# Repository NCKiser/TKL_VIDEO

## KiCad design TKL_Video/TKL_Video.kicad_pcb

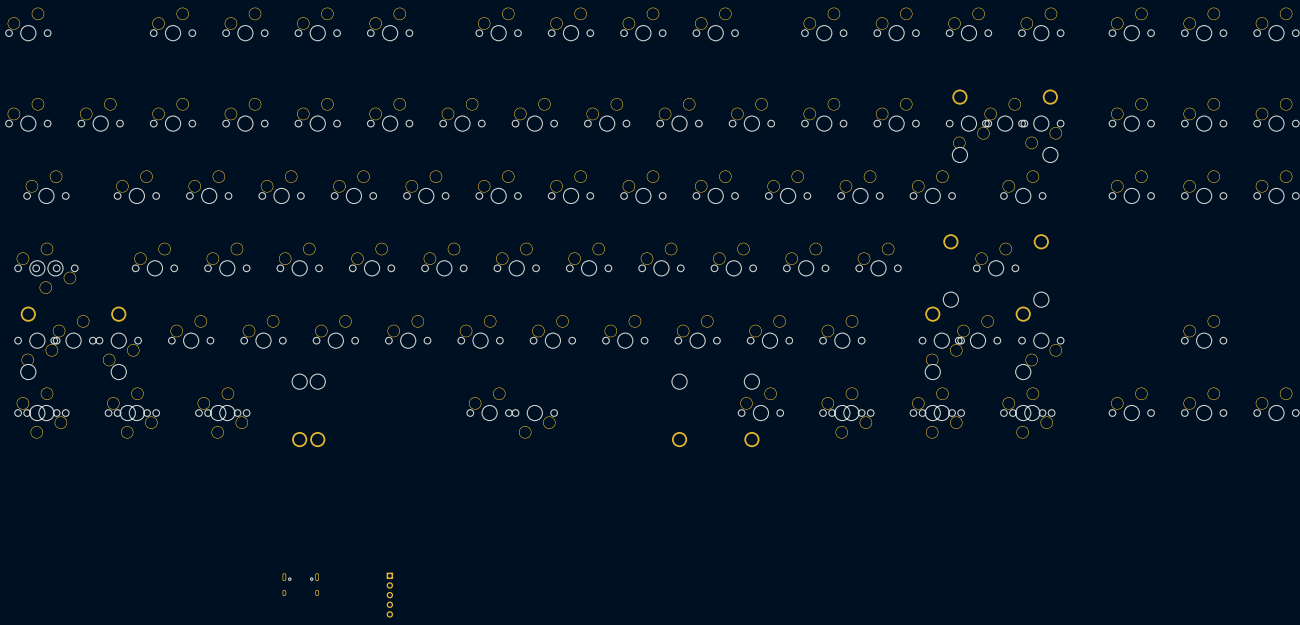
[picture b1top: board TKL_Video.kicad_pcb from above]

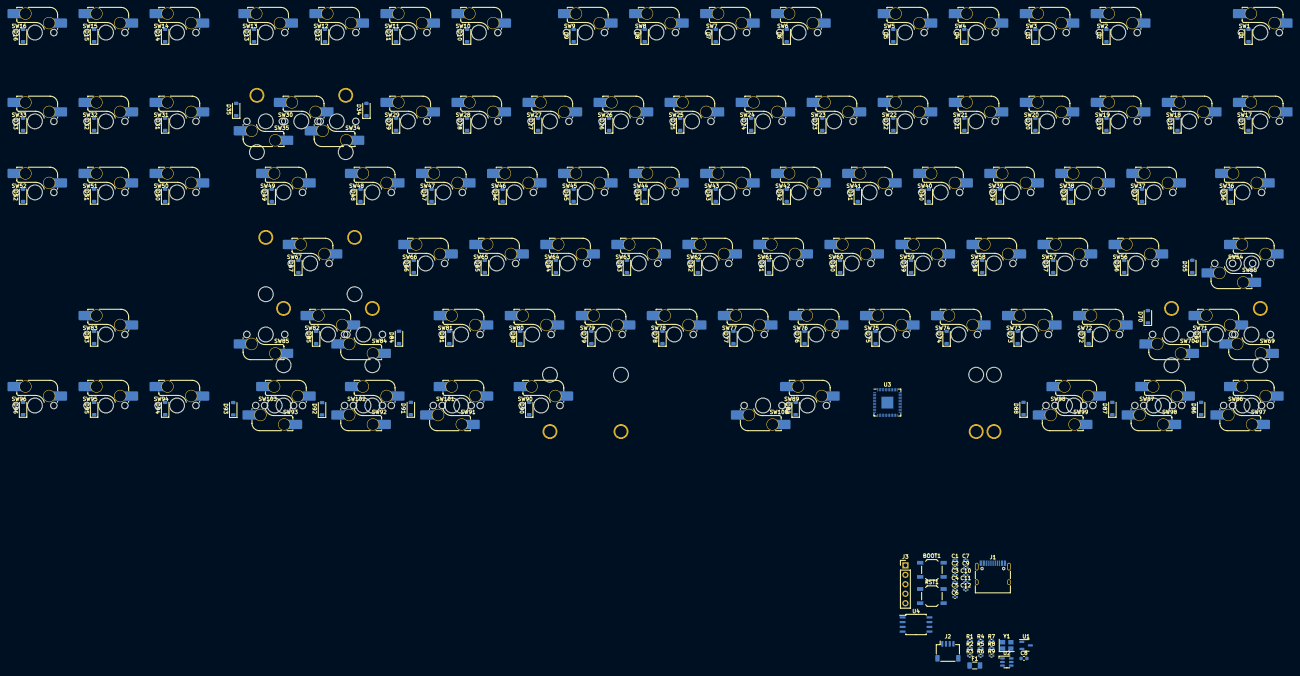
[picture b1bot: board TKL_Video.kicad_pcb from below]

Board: 2 copper layers, 229 parts (223 on the bottom side), 115 nets, no tracks yet.

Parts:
BOOT1: SW_Push; SW_SPST_TL3342
C1, C2, C5, C6, C9: 1u; C_0402_1005Metric
C3, C4: 22p; C_0402_1005Metric
C7, C10, C11, C12: 100n; C_0402_1005Metric
C8: 10u; C_0603_1608Metric
D1, D2, D3, D4, D5, D6, D7, D8, D9, D10, D11, D12, D13, D14, D15, D16, D17, D18, D19, D20, D21, D22, D23, D24, D25, D26, D27, D28, D29, D31, D32, D33, D34, D35, D36, D37, D38, D39, D40, D41, D42, D43, D44, D45, D46, D47, D48, D49, D50, D51, D52, D55, D56, D57, D58, D59, D60, D61, D62, D63, D64, D65, D66, D67, D69, D70, D72, D73, D74, D75, D76, D77, D78, D79, D80, D81, D83, D84, D85, D86, D87, D88, D89, D90, D91, D92, D93, D94, D95, D96: D_Small; D_SOD-123
F1: Fuse_Small; Fuse_1206_3216Metric
J1: USB_C_Receptacle_USB2.0; USB_C_Receptacle_HRO_TYPE-C-31-M-12
J2: Conn_01x04; JST_SH_SM04B-SRSS-TB_1x04-1MP_P1.00mm_Horizontal
J3: Conn_01x05; PinHeader_1x05_P2.54mm_Vertical
R1, R2, R3, R4, R5: 5.1k; R_0402_1005Metric
R6, R7: 1k; R_0402_1005Metric
R8, R9: 27; R_0402_1005Metric
RST1: SW_Push; SW_SPST_TL3342
S1, S5: MX_stab; STAB_MX_P_2.25u
S2: MX_stab; STAB_MX_P_6.25u
S3: MX_stab; STAB_MX_P_7u
S4: MX_stab; STAB_MX_P_2.75u
S6: MX_stab; STAB_MX_P_2u
SW1, SW2, SW3, SW4, SW5, SW6, SW7, SW8, SW9, SW10, SW11, SW12, SW13, SW14, SW15, SW16, SW17, SW18, SW19, SW20, SW21, SW22, SW23, SW24, SW25, SW26, SW27, SW28, SW29, SW30, SW31, SW32, SW33, SW34, SW35, SW37, SW38, SW39, SW40, SW41, SW42, SW43, SW44, SW45, SW46, SW47, SW48, SW50, SW51, SW52, SW56, SW57, SW58, SW59, SW60, SW61, SW62, SW63, SW64, SW65, SW66, SW67, SW70, SW71, SW72, SW73, SW74, SW75, SW76, SW77, SW78, SW79, SW80, SW81, SW82, SW83, SW85, SW89, SW94, SW95, SW96, SW98, SW100, SW102: MX_SW_HS; SW_MX_HS_1u
SW36, SW49, SW97, SW99, SW101, SW103: MX_SW_HS; SW_MX_HS_1.5u
SW54: MX_SW_HS; SW_MX_HS_1.75u_STP_1.25
SW55, SW84: MX_SW_HS; SW_MX_HS_1.75u
SW69, SW86, SW87, SW88, SW90, SW91, SW92, SW93: MX_SW_HS; SW_MX_HS_1.25u
U1: XC6206PxxxMR; SOT-23-3
U2: SRV05-4; SOT-23-6-routable
U3: RP2040; QFN-56-1EP_7x7mm_P0.4mm_EP3.2x3.2mm
U4: W25Q128JVS; SOIC-8_5.23x5.23mm_P1.27mm
Y1: Crystal_GND24; Crystal_SMD_3225-4Pin_3.2x2.5mm

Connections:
+1V1: C6.1, C7.1, U3.23 (DVDD), U3.45 (VREG_VOUT), U3.50 (DVDD)
+3V3: C2.1, C5.1, C8.1, C9.1, C10.1, C11.1, C12.1, J3.2, R3.2, R4.2, U1.2 (VO), U3.1 (IOVDD), U3.10 (IOVDD), U3.22 (IOVDD), U3.33 (IOVDD), U3.42 (IOVDD), U3.43 (ADC_AVDD), U3.44 (VREG_IN), U3.48 (USB_VDD), U3.49 (IOVDD), U4.8 (VCC)
+5V: C1.1, F1.2, J2.1, U1.3 (VI), U2.5 (VP)
D+: J1.A6 (D+), J1.B6 (D+), J2.3, R8.1, U2.1 (IO1)
D-: J1.A7 (D-), J1.B7 (D-), J2.2, R9.1, U2.6 (IO4)
GND: BOOT1.1, C1.2, C2.2, C3.1, C4.1, C5.2, C6.2, C7.2, C8.2, C9.2, C10.2, C11.2, C12.2, J1.A1 (GND), J1.A12 (GND), J1.B1 (GND), J1.B12 (GND), J1.S1 (SHIELD), J2.4, J3.3, R1.2, R2.2, RST1.1, U1.1 (GND), U2.2 (VN), U3.19 (TESTEN), U3.57 (GND), U4.4 (GND), Y1.2, Y1.4
unnamed: BOOT1.2, R6.1
unnamed: C4.2, R7.1, Y1.1
unnamed: D1.2 (A), SW1.2
unnamed: D2.2 (A), SW2.2
unnamed: D3.2 (A), SW3.2
unnamed: D4.2 (A), SW4.2
unnamed: D5.2 (A), SW5.2
unnamed: D6.2 (A), SW6.2
unnamed: D7.2 (A), SW7.2
unnamed: D8.2 (A), SW8.2
unnamed: D9.2 (A), SW9.2
unnamed: D10.2 (A), SW10.2
unnamed: D11.2 (A), SW11.2
unnamed: D12.2 (A), SW12.2
unnamed: D13.2 (A), SW13.2
unnamed: D14.2 (A), SW14.2
unnamed: D15.2 (A), SW15.2
unnamed: D16.2 (A), SW16.2
unnamed: D17.2 (A), SW17.2
unnamed: D18.2 (A), SW18.2
unnamed: D19.2 (A), SW19.2
unnamed: D20.2 (A), SW20.2
unnamed: D21.2 (A), SW21.2
unnamed: D22.2 (A), SW22.2
unnamed: D23.2 (A), SW23.2
unnamed: D24.2 (A), SW24.2
unnamed: D25.2 (A), SW25.2
unnamed: D26.2 (A), SW26.2
unnamed: D27.2 (A), SW27.2
unnamed: D28.2 (A), SW28.2
unnamed: D29.2 (A), SW29.2
unnamed: D31.2 (A), SW31.2
unnamed: D32.2 (A), SW32.2
unnamed: D33.2 (A), SW33.2
unnamed: D34.2 (A), SW34.2
unnamed: D35.2 (A), SW35.2
unnamed: D36.2 (A), SW36.2
unnamed: D37.2 (A), SW37.2
unnamed: D38.2 (A), SW38.2
unnamed: D39.2 (A), SW39.2
unnamed: D40.2 (A), SW40.2
unnamed: D41.2 (A), SW41.2
unnamed: D42.2 (A), SW42.2
unnamed: D43.2 (A), SW43.2
unnamed: D44.2 (A), SW44.2
unnamed: D45.2 (A), SW45.2
unnamed: D46.2 (A), SW46.2
unnamed: D47.2 (A), SW47.2
unnamed: D48.2 (A), SW48.2
unnamed: D49.2 (A), SW49.2
unnamed: D50.2 (A), SW50.2
unnamed: D51.2 (A), SW51.2
unnamed: D52.2 (A), SW52.2
unnamed: D55.2 (A), SW55.2
unnamed: D56.2 (A), SW56.2
unnamed: D57.2 (A), SW57.2
unnamed: D58.2 (A), SW58.2
unnamed: D59.2 (A), SW59.2
unnamed: D60.2 (A), SW60.2
unnamed: D61.2 (A), SW61.2
unnamed: D62.2 (A), SW62.2
unnamed: D63.2 (A), SW63.2
unnamed: D64.2 (A), SW64.2
unnamed: D65.2 (A), SW65.2
unnamed: D66.2 (A), SW66.2
unnamed: D67.2 (A), SW67.2
unnamed: D69.2 (A), SW69.2
unnamed: D70.2 (A), SW70.2
unnamed: D72.2 (A), SW72.2
unnamed: D73.2 (A), SW73.2
unnamed: D74.2 (A), SW74.2
unnamed: D75.2 (A), SW75.2
unnamed: D76.2 (A), SW76.2
unnamed: D77.2 (A), SW77.2
unnamed: D78.2 (A), SW78.2
unnamed: D79.2 (A), SW79.2
unnamed: D80.2 (A), SW80.2
unnamed: D81.2 (A), SW81.2
unnamed: D83.2 (A), SW83.2
unnamed: D84.2 (A), SW84.2
unnamed: D85.2 (A), SW85.2
unnamed: D86.2 (A), SW86.2
unnamed: D87.2 (A), SW87.2
unnamed: D88.2 (A), SW88.2
unnamed: D89.2 (A), SW89.2
unnamed: D90.2 (A), SW90.2
unnamed: D91.2 (A), SW91.2
unnamed: D92.2 (A), SW92.2
unnamed: D93.2 (A), SW93.2
unnamed: D94.2 (A), SW94.2
unnamed: D95.2 (A), SW95.2
unnamed: D96.2 (A), SW96.2
unnamed: J1.A5 (CC1), R1.1
unnamed: J1.B5 (CC2), R2.1
unnamed: R4.1, R5.2
unnamed: R9.2, U3.46 (USB_DM)
unnamed: R8.2, U3.47 (USB_DP)
Q_CLK: U3.52 (QSPI_SCLK), U4.6 (CLK)
Q_IO0: U3.53 (QSPI_SD0), U4.5 (DI(IO0))
Q_IO1: U3.55 (QSPI_SD1), U4.2 (DO(IO1))
Q_IO2: U3.54 (QSPI_SD2), U4.3 (IO2)
Q_IO3: U3.51 (QSPI_SD3), U4.7 (IO3)
Q_SEL: R5.1, R6.2, U3.56 (QSPI_SS), U4.1 (~CS)
RESET: J3.1, R3.1, RST1.2, U3.26 (RUN)
SWC: J3.4, U3.24 (SWCLK)
SWD: J3.5, U3.25 (SWD)
VBUS: F1.1, J1.A4 (VBUS), J1.A9 (VBUS), J1.B4 (VBUS), J1.B9 (VBUS)
XIN: C3.2, U3.20 (XIN), Y1.3
XOUT: R7.2, U3.21 (XOUT)

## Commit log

2023-05-23 Add PCB Schematic for first video
2023-05-31 Video Part 2
